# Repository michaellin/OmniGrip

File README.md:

## Description
The OmniGrip is a master manipulator gripper device capable of rendering a programmed stiffness. This open source project aims to add a seventh degree of freedom to the conventional Sensable Touch (Phantom Omni) haptic device. The project's files can be found at our [github repository](https://github.com/michaellin/OmniGrip). There are two versions of the device. The RE model uses a [Maxon RE-25 Motor](http://www.engr.ucsb.edu/~mdnip/me170c/datasheets/25mm_Motors.pdf) and the A-Max model uses a [Maxon A-Max-22 Motor](http://www.farnell.com/datasheets/484760.pdf). NOTE: the software currently only supports the RE model. It has not been tested for the A-Max model yet. For more details about the device refer to the conference paper: <link to future paper>.

## Assembly Instructions
List of materials needed to assemble the OmniGrip:

(quantity) description [McMaster-Carr part number]

1. (8) 3D printed parts of the device
  1. Long lever
  2. Short lever
  3. Frame center piece
  4. Frame top piece
  5. Frame bottom piece
  6. Long capstan gear
  7. Short capstan gear
  8. Handle
2. (6) Mini High-Precision Ball Bearing - ABEC-5                                                                [MC 57155K355]
3. (1) 10 Ft. Type 304 Stainless Steel Wire Rope, 7x19 Strand Core, 0.024" Dia, 70 Lb Break Strength, 10' Long  [MC 3461T621]
4. (2) Vented 18-8 Ss Socket Head Cap Screw, 4-40 Thread, 1/2" Length, .035" Vent Diameter                      [MC 93235A110]
5. (8) Type 316 Ss Socket Head Cap Screw, 0-80 Thread, 1/4" Long                                                [MC 92185A053]
6. (8) Brass Press-Fit Expansion Insert for Plastics without Flange, 0-80 Internal Thread, 1/8" Length          [MC 92395A109]
7. (2) Type 316 Stainless Steel Socket Head Cap Screw, 2-56 Thread, 1/4" Length                                 [MC 92185A077]
8. (2) Brass Press-Fit Expansion Insert for Plastics without Flange, 2-56 Internal Thread, 5/32" Length         [MC 92395A111]
9. (3) Metric 316 Stainless Steel Pan Head Phillips Machine Screw, M2 Size, 5mm Length, .4mm Pitch              [MC 90116A009]
10. (2) Copper Oval Compression Sleeve for 1/32" Rope Diameter, 1/4" Sleeve Length                              [MC 3897T31]

Important Note: most McMaster-Carr parts come in packs. The number specified in the parenthesis is just the amount of units used, not the number of packs you need to buy.

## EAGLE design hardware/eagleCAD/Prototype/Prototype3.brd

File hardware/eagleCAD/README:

When using EagleCAD to open the Prototype layouts, some references might be broken initially. Relocate the files in "./lib/SparkFun-*". (* means wildcard/anything)

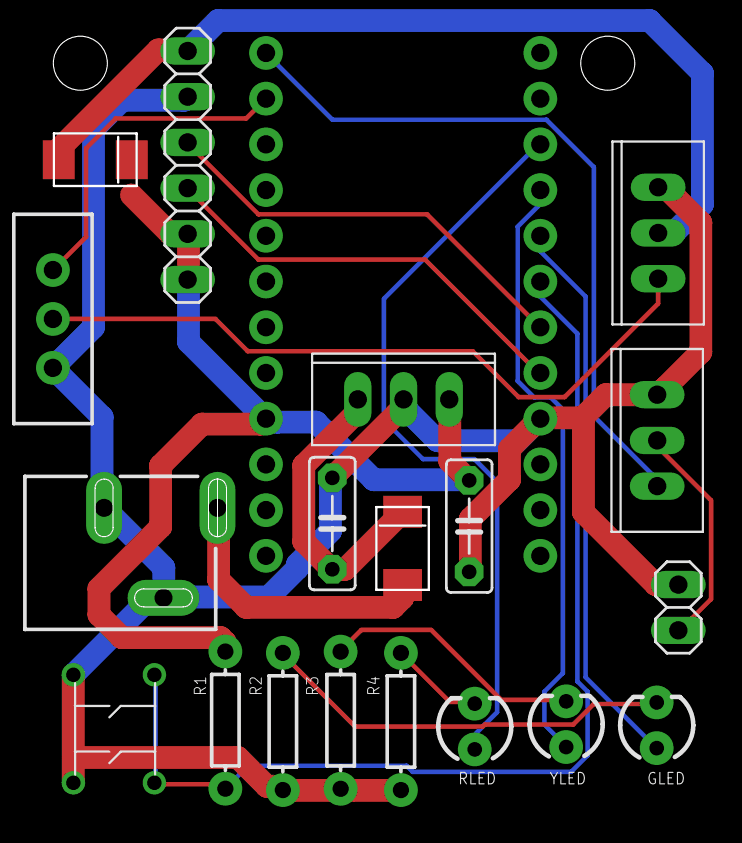
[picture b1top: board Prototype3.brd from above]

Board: 2 copper layers, 20 parts (0 on the bottom side), 18 nets.

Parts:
C1: 0.1uF; C5B2.5
C2: 0.33uF; C5B2.5
D1: SCHOTTKY-DIODE; SMD-DIODE
GLED: LED3MM
IC1: LM7805; TO-220(2)
J1: POWER_JACKSLT; POWER_JACK_SLOT
JACK: 1X02
JP2: 1X06
R1, R2, R3, R4: AXIAL-0.3
RLED: LED3MM
S1: SWITCH-SPDT_KIT
U$1: SCHOTTKY-DIODE; SMD-DIODE
U$2: ARDUINO_MINI
U$3: PUSH-BUTTON; PUSHBTTN
U$4, U$5: IRLZ34; TO-220(2)
YLED: LED3MM

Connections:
CH_A: JP2.3, U$2.5
CH_B: JP2.4, U$2.6
GND: C1.2, C2.2, IC1.GND, J1.GND@1, J1.GND@2, JACK.2, JP2.5, R2.P$1, R3.P$1, R4.P$1, S1.1, U$2.4, U$3.P$1, U$3.P$4, U$4.OUT, U$5.OUT
J_PWM: U$2.13, U$5.IN
M-: JP2.6, U$1.P$1, U$4.GND
M_PWM: S1.3, U$2.14
unnamed: JACK.1, U$5.GND
unnamed: D1.P$1, J1.PWR
unnamed: S1.2, U$4.IN
unnamed: C2.1, D1.P$2, IC1.IN
unnamed: R4.P$2, RLED.K
unnamed: R3.P$2, YLED.K
unnamed: GLED.K, R2.P$2
unnamed: GLED.A, U$2.8
unnamed: U$2.9, YLED.A
unnamed: RLED.A, U$2.10
unnamed: R1.P$2, U$2.7, U$3.P$2, U$3.P$3
VDD: C1.1, IC1.OUT, JP2.1, JP2.2, R1.P$1, U$1.P$2, U$2.21

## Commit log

2014-10-16 Adding Solidworks parts
2014-10-16 Re-adding hardware files
2014-10-16 Adding gitignore
2014-10-16 Adding readme
2014-10-16 Adding more into the README
2014-10-16 removing lose file
2014-10-16 cleaning up more
2014-10-16 Adding some libraries
2014-10-16 removing some lingering files
2015-01-20 adding materials list to readme
2015-01-20 more on readme
2015-03-11 fixing solidworks problems using pack and go.
2015-05-26 adding more to the materials list
2015-05-26 fixing the itemizing
2015-05-26 more fix to itemizing

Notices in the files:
parts and their libraries:
SparkFun: Licensing: CC v3.0 Share-Alike You are welcome to use this library for commercial purposes.
SparkFun-LED: Licensing: Creative Commons ShareAlike 4.0 International - https://creativecommons.org/licenses/by-sa/4.0
